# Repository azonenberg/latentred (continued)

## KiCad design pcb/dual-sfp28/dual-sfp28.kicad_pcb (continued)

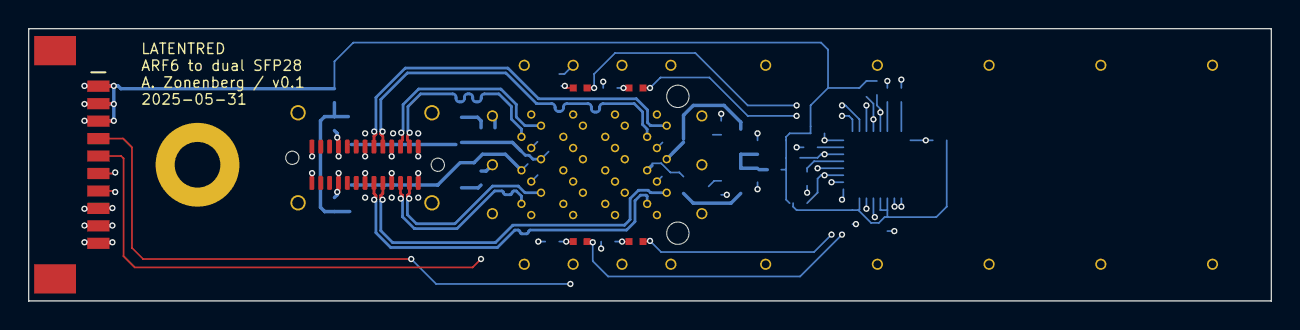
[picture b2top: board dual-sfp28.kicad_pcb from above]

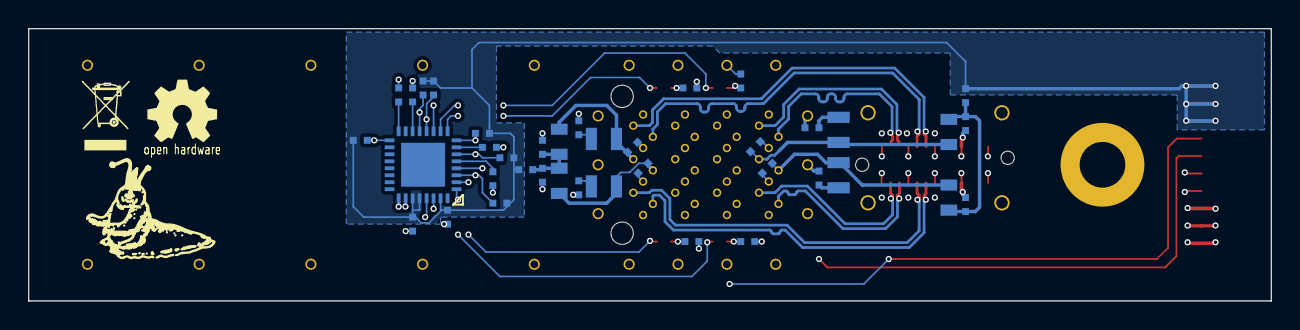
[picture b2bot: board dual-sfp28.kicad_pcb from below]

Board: 4 copper layers, 89.0 x 19.5 mm, 50 parts (42 on the bottom side), 48 nets.

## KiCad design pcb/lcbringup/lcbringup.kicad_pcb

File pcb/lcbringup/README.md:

# lcbringup

This is a bringup test fixture for validating the line card (in conjunction with my kup-lulz XCKU5P FPGA board) and not intended to be part of the final LATENTED system.

Known errata: MDIO and MDC are on ball locations that are NC in the 7a35t FGG484 package. Reworked board connecting MDIO to the SPI pins on the adjacent bank and added external level shifters.

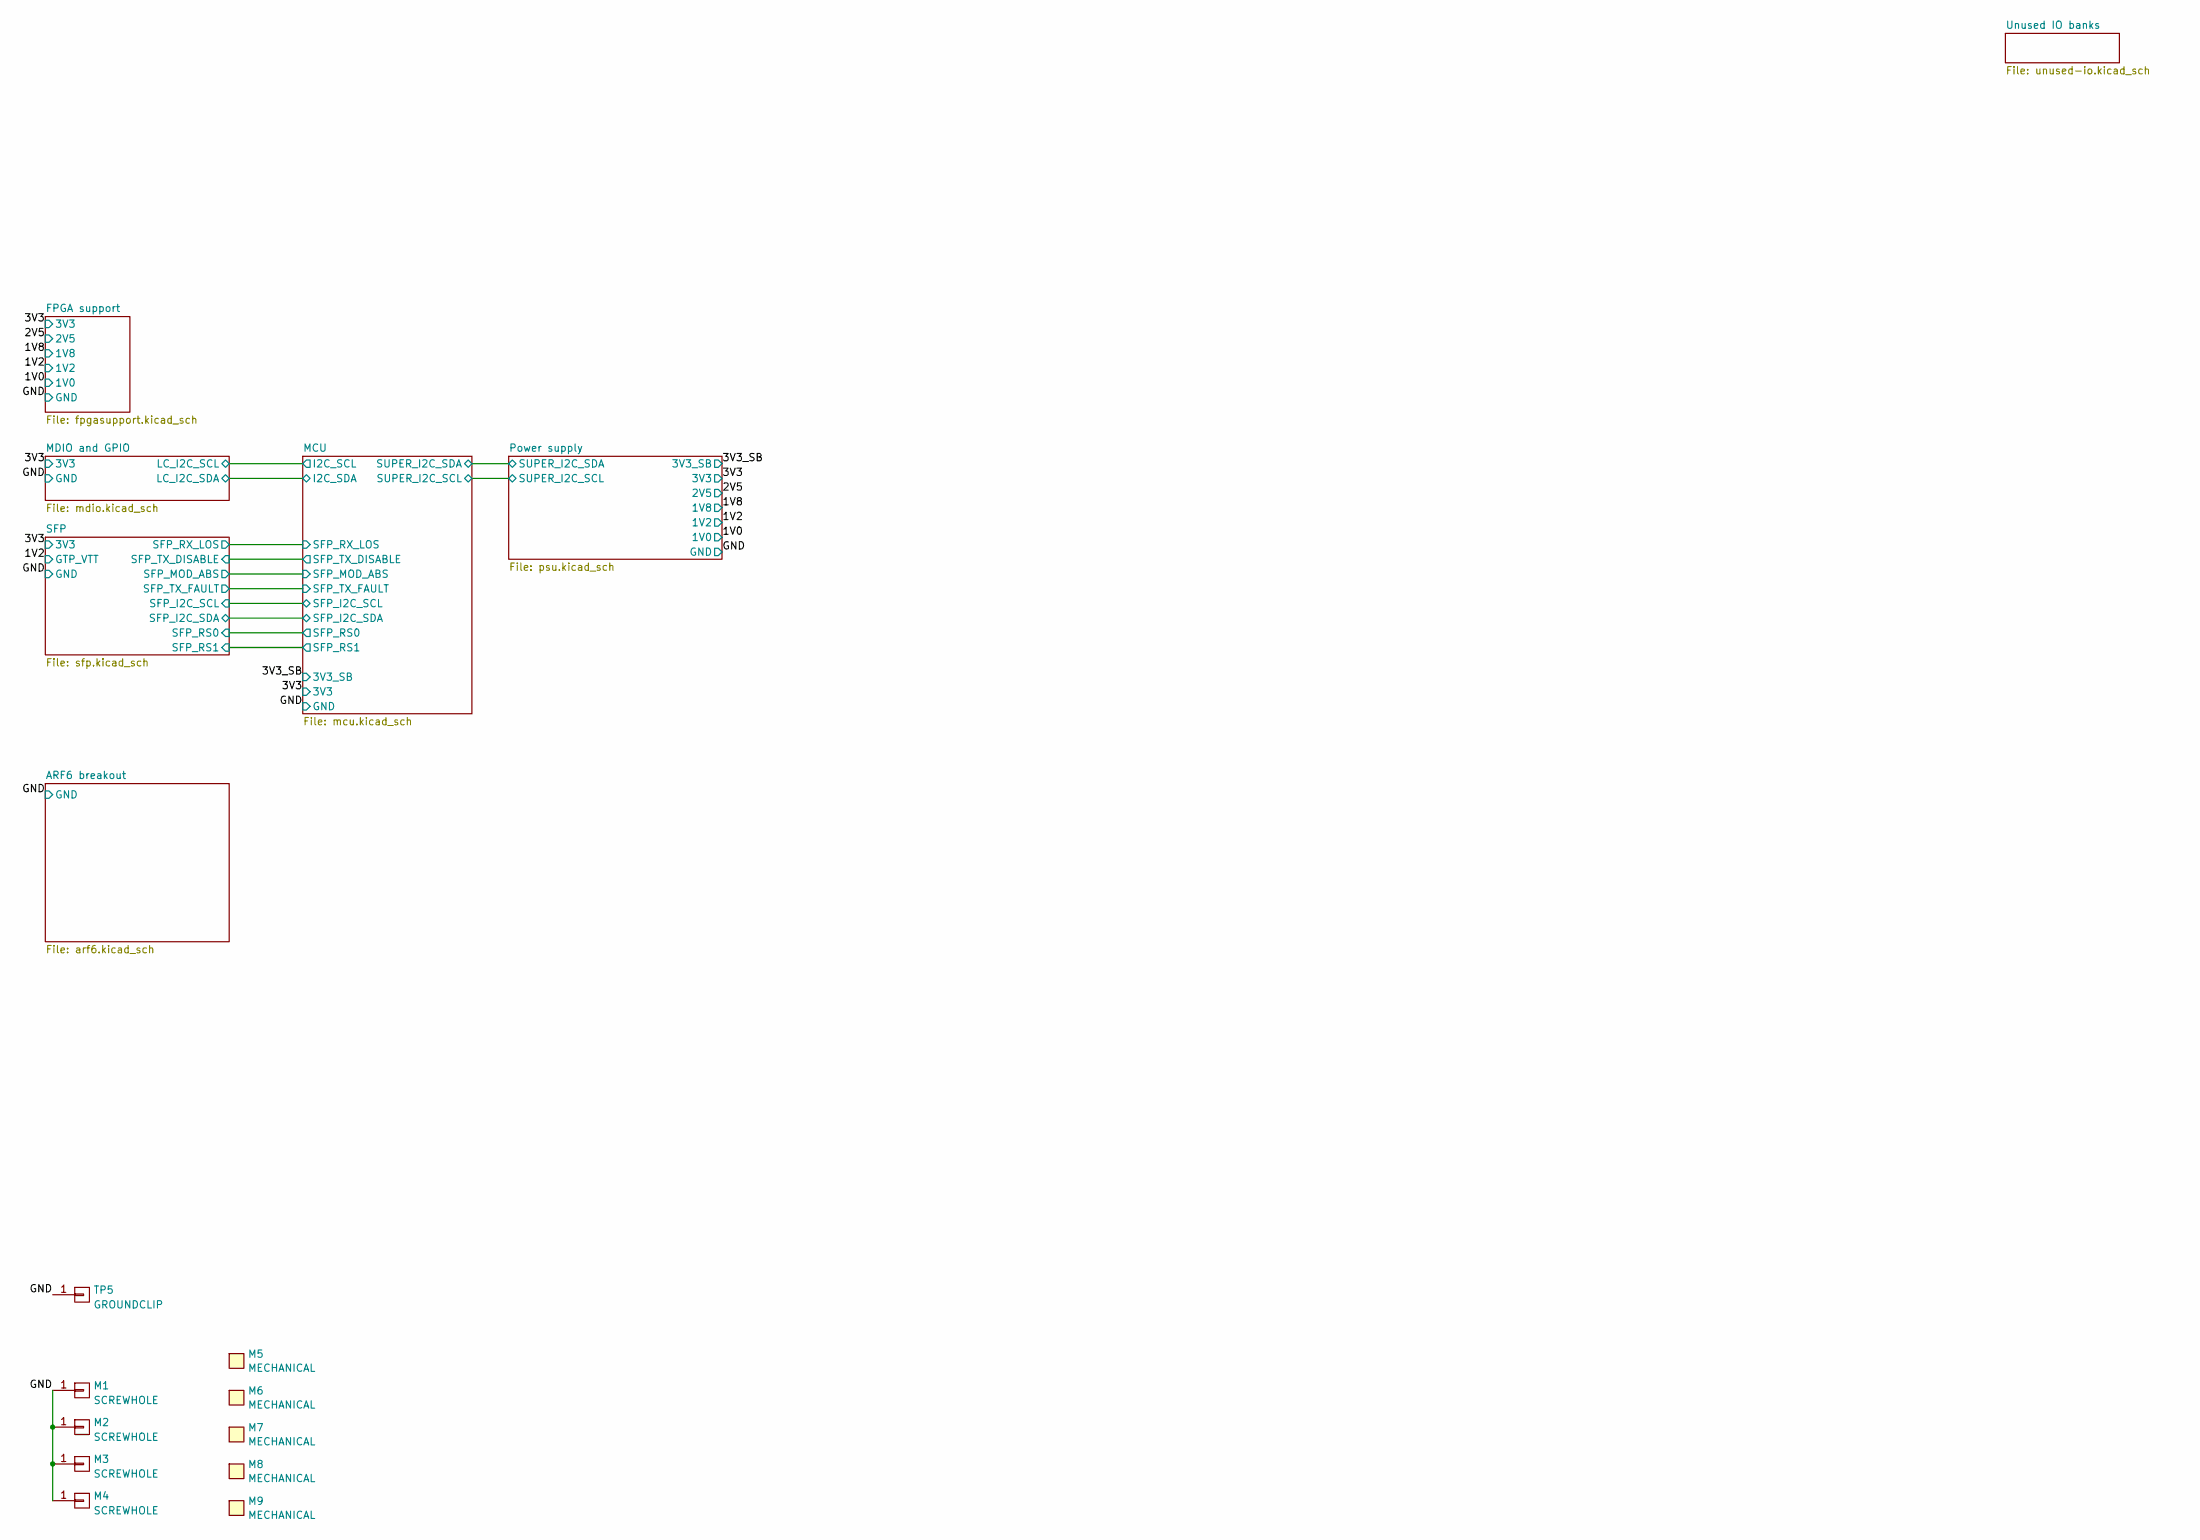
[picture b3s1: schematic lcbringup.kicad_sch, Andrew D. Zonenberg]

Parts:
M1, M2, M3, M4: SCREWHOLE; MECHANICAL_CLEARANCEHOLE_4_40
M5: MECHANICAL; LONGTHING-1200DPI
M6: MECHANICAL; LOGO_ESD_SENSITIVE_7MM
M7: MECHANICAL; Logo_silk_OSHW_6x6mm
M8: MECHANICAL; Logo_silk_ROHS_5x2.8mm
M9: MECHANICAL; Logo_silk_WEEE_3.4x5mm
TP5: GROUNDCLIP; TESTPOINT_SMT_KEYSTONE_5016

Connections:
/GND: M1.1, M2.1, M3.1, M4.1, TP5.1; also elsewhere on the board

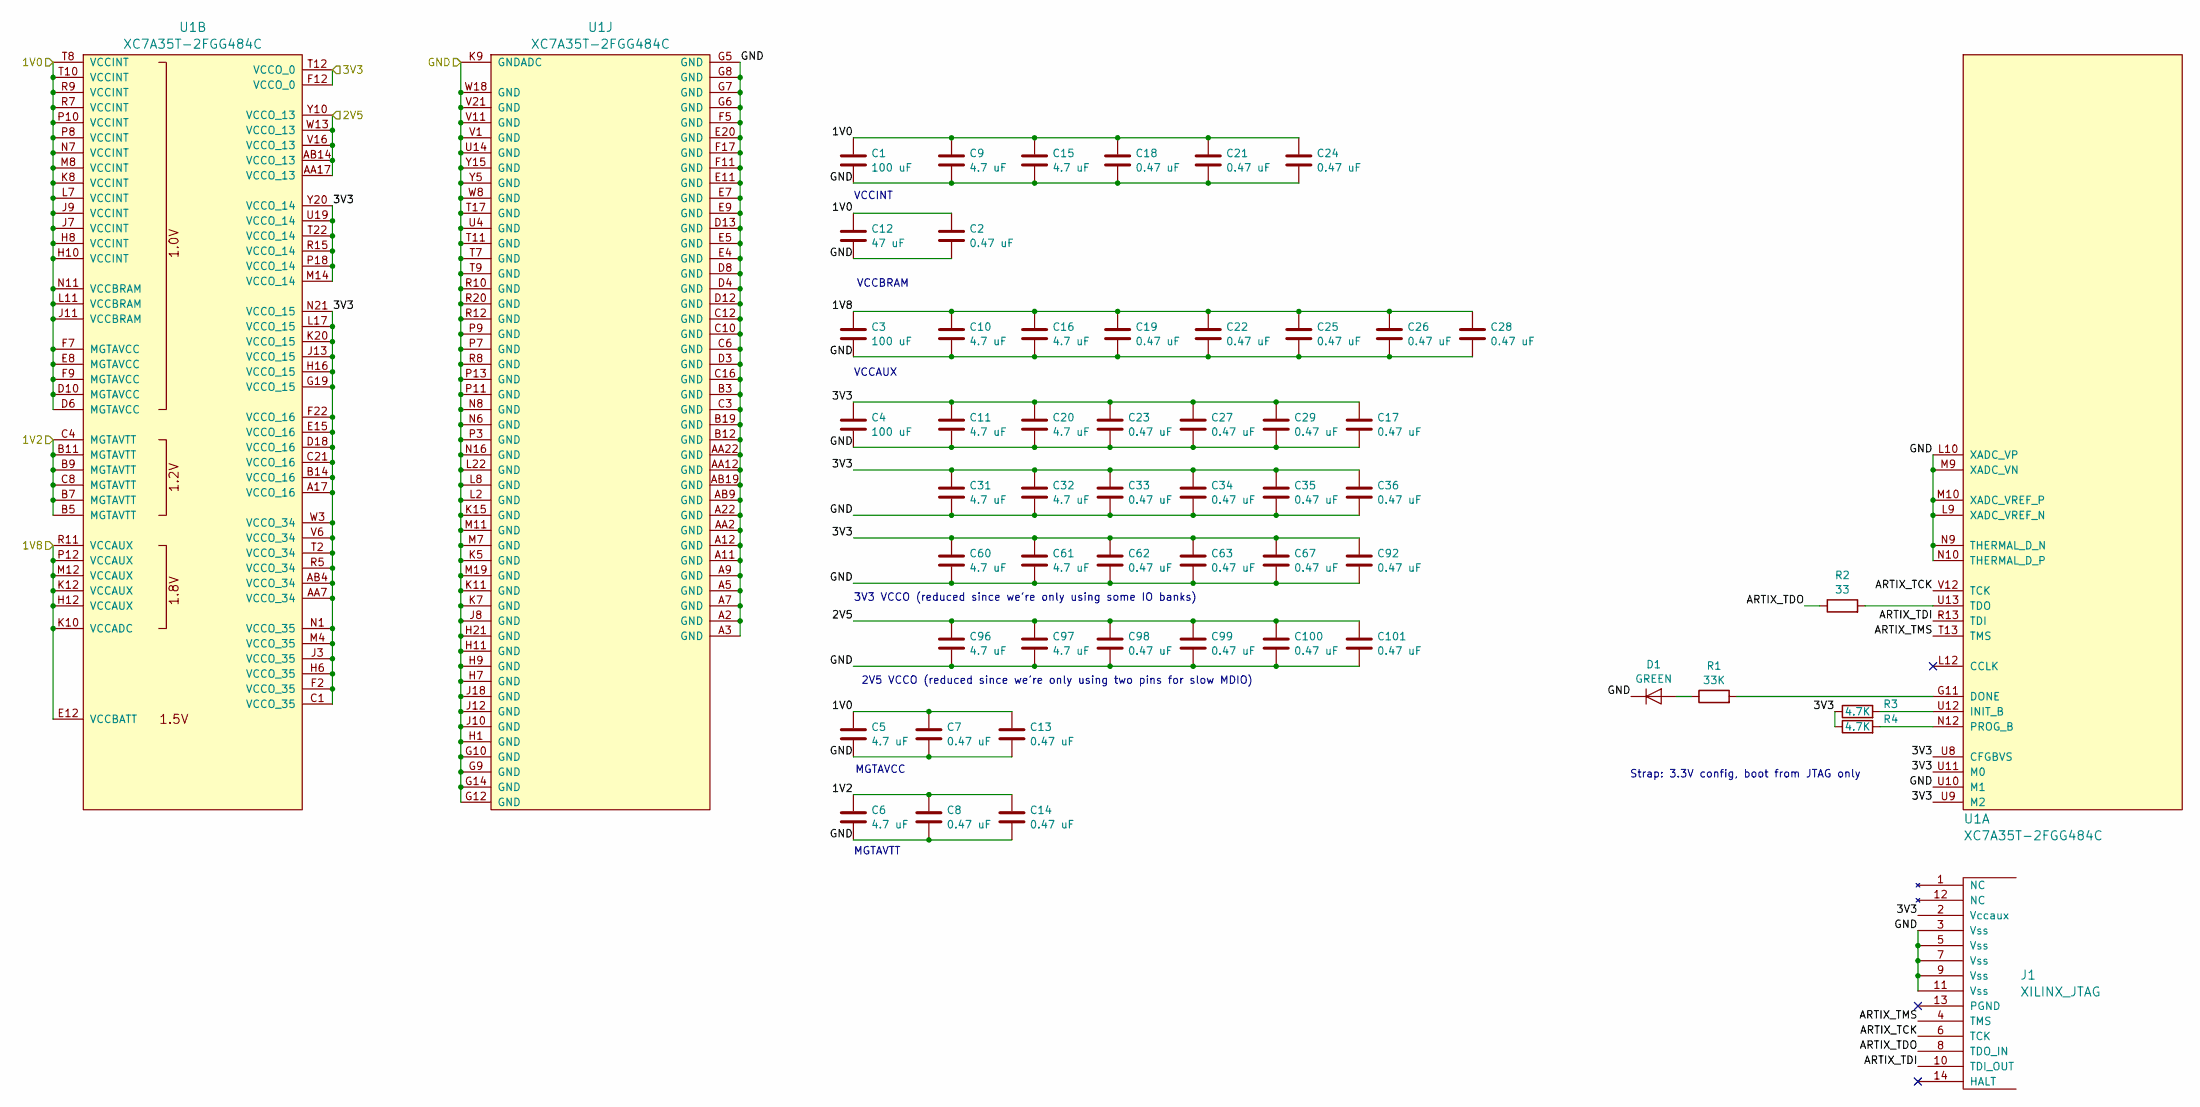
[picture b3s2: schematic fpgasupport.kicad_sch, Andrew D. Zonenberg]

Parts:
C1, C3, C4: 100 uF; EIA_1210_CAP_NOSILK
C2, C7, C8, C13, C14, C17, C18, C19, C21, C22, C23, C24, C25, C26, C27, C28, C29, C33, C34, C35, C36, C62, C63, C67, C92, C98, C99, C100, C101: 0.47 uF; EIA_0402_CAP_NOSILK
C5, C6, C9, C10, C11, C15, C16, C20, C31, C32, C60, C61, C96, C97: 4.7 uF; EIA_0603_CAP_NOSILK
C12: 47 uF; EIA_1210_CAP_NOSILK
D1: GREEN; EIA_0402_LED
J1: XILINX_JTAG; XILINX_JTAG_PTH_MOLEX_0878311420
R1: 33K; EIA_0402_RES_NOSILK
R2: 33; EIA_0402_RES_NOSILK
R3, R4: 4.7K; EIA_0402_RES_NOSILK
U1: XC7A35T-2FGG484C; BGA_484_22x22_FULLARRAY_1MM

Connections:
/1V0: C1.1, C2.1, C5.1, C7.1, C9.1, C12.1, C13.1, C15.1, C18.1, C21.1, C24.1, U1.D6 (MGTAVCC), U1.D10 (MGTAVCC), U1.E8 (MGTAVCC), U1.F7 (MGTAVCC), U1.F9 (MGTAVCC), U1.H8 (VCCINT), U1.H10 (VCCINT), U1.J7 (VCCINT), U1.J9 (VCCINT), U1.J11 (VCCBRAM), U1.K8 (VCCINT), U1.L7 (VCCINT), U1.L11 (VCCBRAM), U1.M8 (VCCINT), U1.N7 (VCCINT), U1.N11 (VCCBRAM), U1.P8 (VCCINT), U1.P10 (VCCINT), U1.R7 (VCCINT), U1.R9 (VCCINT), U1.T8 (VCCINT), U1.T10 (VCCINT); also elsewhere on the board
/1V2: C6.1, C8.1, C14.1, U1.B5 (MGTAVTT), U1.B7 (MGTAVTT), U1.B9 (MGTAVTT), U1.B11 (MGTAVTT), U1.C4 (MGTAVTT), U1.C8 (MGTAVTT); also elsewhere on the board
/1V8: C3.1, C10.1, C16.1, C19.1, C22.1, C25.1, C26.1, C28.1, U1.E12 (VCCBATT), U1.H12 (VCCAUX), U1.K10 (VCCADC), U1.K12 (VCCAUX), U1.M12 (VCCAUX), U1.P12 (VCCAUX), U1.R11 (VCCAUX); also elsewhere on the board
/2V5: C96.1, C97.1, C98.1, C99.1, C100.1, C101.1, U1.AA17 (VCCO_13), U1.AB14 (VCCO_13), U1.V16 (VCCO_13), U1.W13 (VCCO_13), U1.Y10 (VCCO_13); also elsewhere on the board
/3V3: C4.1, C11.1, C17.1, C20.1, C23.1, C27.1, C29.1, C31.1, C32.1, C33.1, C34.1, C35.1, C36.1, C60.1, C61.1, C62.1, C63.1, C67.1, C92.1, J1.2 (Vccaux), R3.1, R4.1, U1.A17 (VCCO_16), U1.AA7 (VCCO_34), U1.AB4 (VCCO_34), U1.B14 (VCCO_16), U1.C1 (VCCO_35), U1.C21 (VCCO_16), U1.D18 (VCCO_16), U1.E15 (VCCO_16), U1.F2 (VCCO_35), U1.F12 (VCCO_0), U1.F22 (VCCO_16), U1.G19 (VCCO_15), U1.H6 (VCCO_35), U1.H16 (VCCO_15), U1.J3 (VCCO_35), U1.J13 (VCCO_15), U1.K20 (VCCO_15), U1.L17 (VCCO_15), U1.M4 (VCCO_35), U1.M14 (VCCO_14), U1.N1 (VCCO_35), U1.N21 (VCCO_15), U1.P18 (VCCO_14), U1.R5 (VCCO_34), U1.R15 (VCCO_14), U1.T2 (VCCO_34), U1.T12 (VCCO_0), U1.T22 (VCCO_14), U1.U8 (CFGBVS), U1.U9 (M2), U1.U11 (M0), U1.U19 (VCCO_14), U1.V6 (VCCO_34), U1.W3 (VCCO_34), U1.Y20 (VCCO_14); also elsewhere on the board
/FPGA support/ARTIX_TCK: J1.6 (TCK), U1.V12 (TCK)
/FPGA support/ARTIX_TDI: J1.10 (TDI_OUT), U1.R13 (TDI)
/FPGA support/ARTIX_TDO: J1.8 (TDO_IN), R2.1
/FPGA support/ARTIX_TMS: J1.4 (TMS), U1.T13 (TMS)
/GND: C1.2, C2.2, C3.2, C4.2, C5.2, C6.2, C7.2, C8.2, C9.2, C10.2, C11.2, C12.2, C13.2, C14.2, C15.2, C16.2, C17.2, C18.2, C19.2, C20.2, C21.2, C22.2, C23.2, C24.2, C25.2, C26.2, C27.2, C28.2, C29.2, C31.2, C32.2, C33.2, C34.2, C35.2, C36.2, C60.2, C61.2, C62.2, C63.2, C67.2, C92.2, C96.2, C97.2, C98.2, C99.2, C100.2, C101.2, D1.1 (K), J1.3 (Vss), J1.5 (Vss), J1.7 (Vss), J1.9 (Vss), J1.11 (Vss), U1.A2 (GND), U1.A3 (GND), U1.A5 (GND), U1.A7 (GND), U1.A9 (GND), U1.A11 (GND), U1.A12 (GND), U1.A22 (GND), U1.AA2 (GND), U1.AA12 (GND), U1.AA22 (GND), U1.AB9 (GND), U1.AB19 (GND), U1.B3 (GND), U1.B12 (GND), U1.B19 (GND), U1.C3 (GND), U1.C6 (GND), U1.C10 (GND), U1.C12 (GND), U1.C16 (GND), U1.D3 (GND), U1.D4 (GND), U1.D8 (GND), U1.D12 (GND), U1.D13 (GND), U1.E4 (GND), U1.E5 (GND), U1.E7 (GND), U1.E9 (GND), U1.E11 (GND), U1.E20 (GND), U1.F5 (GND), U1.F11 (GND), U1.F17 (GND), U1.G5 (GND), U1.G6 (GND), U1.G7 (GND), U1.G8 (GND), U1.G9 (GND), U1.G10 (GND), U1.G12 (GND), U1.G14 (GND), U1.H1 (GND), U1.H7 (GND), U1.H9 (GND), U1.H11 (GND), U1.H21 (GND), U1.J8 (GND), U1.J10 (GND), U1.J12 (GND), U1.J18 (GND), U1.K5 (GND), U1.K7 (GND), U1.K9 (GNDADC), U1.K11 (GND), U1.K15 (GND), U1.L2 (GND), U1.L8 (GND), U1.L9 (XADC_VREF_N), U1.L10 (XADC_VP), U1.L22 (GND), U1.M7 (GND), U1.M9 (XADC_VN), U1.M10 (XADC_VREF_P), U1.M11 (GND), U1.M19 (GND), U1.N6 (GND), U1.N8 (GND), U1.N9 (THERMAL_D_N), U1.N10 (THERMAL_D_P), U1.N16 (GND), U1.P3 (GND), U1.P7 (GND), U1.P9 (GND), U1.P11 (GND), U1.P13 (GND), U1.R8 (GND), U1.R10 (GND), U1.R12 (GND), U1.R20 (GND), U1.T7 (GND), U1.T9 (GND), U1.T11 (GND), U1.T17 (GND), U1.U4 (GND), U1.U10 (M1), U1.U14 (GND), U1.V1 (GND), U1.V11 (GND), U1.V21 (GND), U1.W8 (GND), U1.W18 (GND), U1.Y5 (GND), U1.Y15 (GND); also elsewhere on the board
unnamed: D1.2 (A), R1.1
unnamed: R1.2, U1.G11 (DONE)
unnamed: R3.2, U1.U12 (INIT_B)
unnamed: R4.2, U1.N12 (PROG_B)
unnamed: R2.2, U1.U13 (TDO)

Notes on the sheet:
Strap: 3.3V config, boot from JTAG only
2V5 VCCO (reduced since we're only using two pins for slow MDIO)
VCCAUX
VCCINT
3V3 VCCO (reduced since we're only using some IO banks)
MGTAVTT
VCCBRAM
MGTAVCC

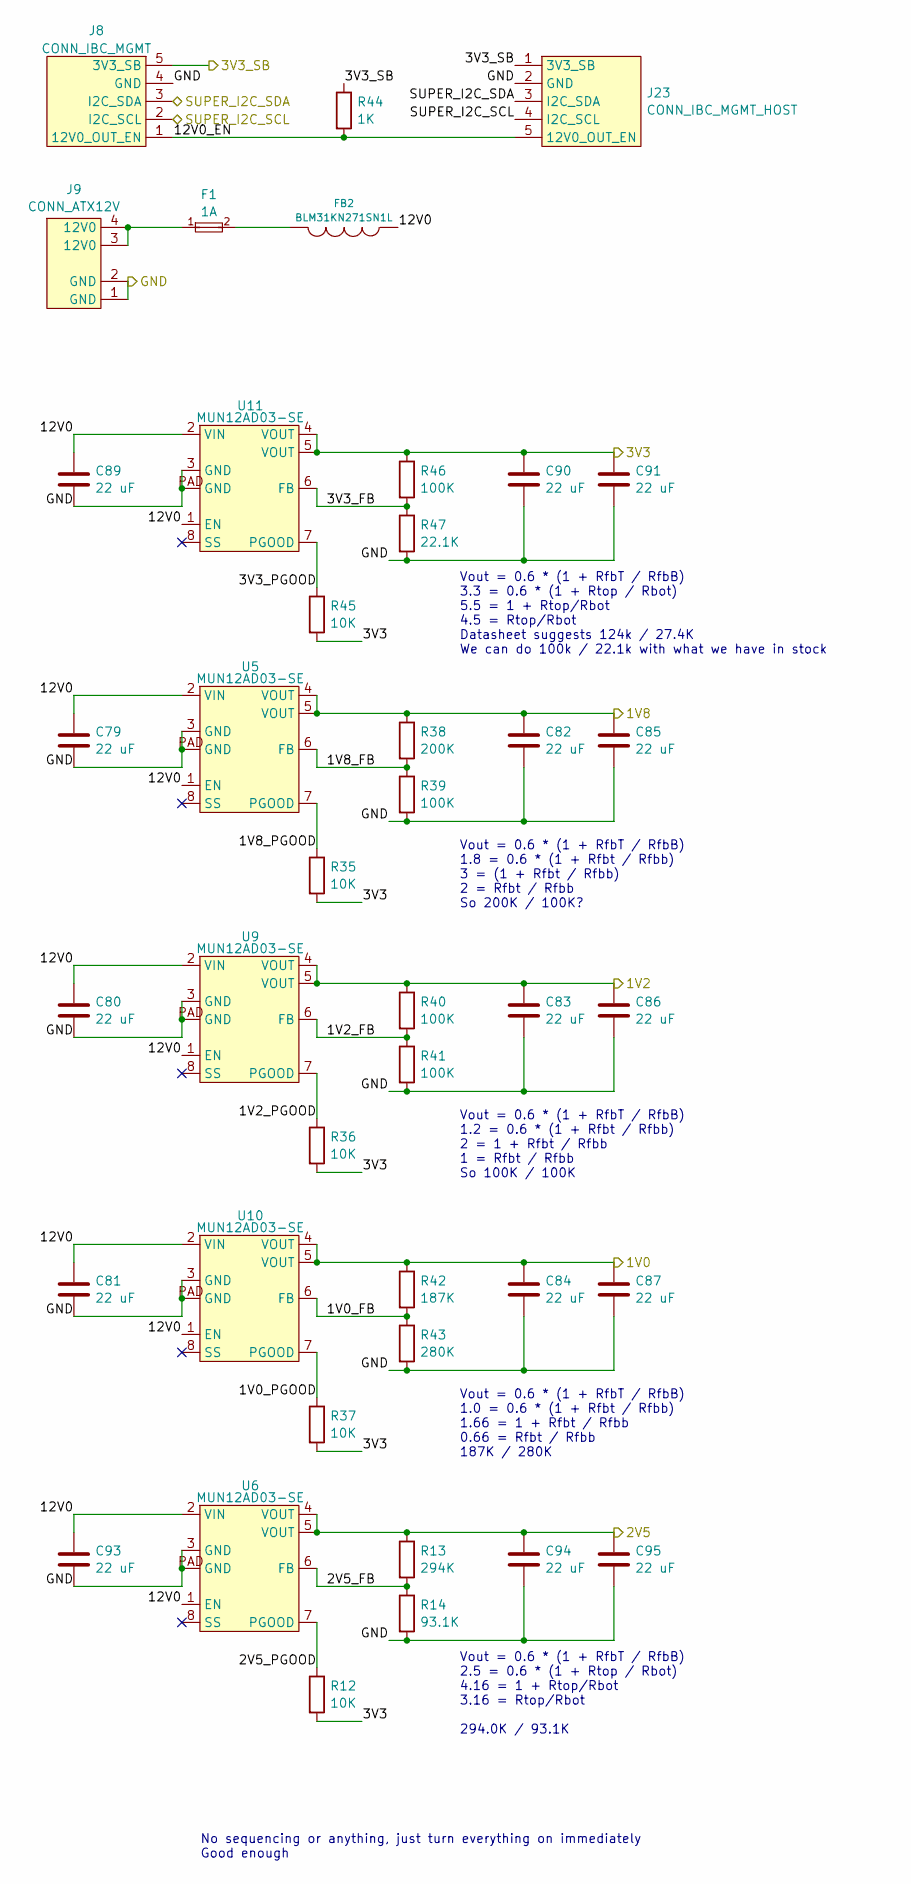
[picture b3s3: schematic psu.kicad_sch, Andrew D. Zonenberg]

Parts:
C79, C80, C81, C89, C93: 22 uF; EIA_1812_CAP_NOSILK
C82, C83, C84, C85, C86, C87, C90, C91, C94, C95: 22 uF; EIA_1210_CAP_NOSILK
F1: 1A; EIA_0402_RES_NOSILK
FB2: BLM31KN271SN1L; EIA_1206_CAP_NOSILK
J8: CONN_IBC_MGMT; CONN_MOLEX_PICOBLADE_5POS_0532610571
J9: CONN_ATX12V; CONN_MOLEX_MINIFITJR_4POS_0039291048
J23: CONN_IBC_MGMT_HOST; CONN_MOLEX_PICOBLADE_5POS_0532610571
R12, R35, R36, R37, R45: 10K; EIA_0402_RES_NOSILK
R13: 294K; EIA_0402_RES_NOSILK
R14: 93.1K; EIA_0402_RES_NOSILK
R38: 200K; EIA_0402_RES_NOSILK
R39, R40, R41, R46: 100K; EIA_0402_RES_NOSILK
R42: 187K; EIA_0402_RES_NOSILK
R43: 280K; EIA_0402_RES_NOSILK
R44: 1K; EIA_0402_RES_NOSILK
R47: 22.1K; EIA_0402_RES_NOSILK
U5, U6, U9, U10, U11: MUN12AD03-SE; MODULE_CYNTEC_MUN12AD03-SE

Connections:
/1V0: C84.1, C87.1, R42.1, U10.4 (VOUT), U10.5 (VOUT); also elsewhere on the board
/1V2: C83.1, C86.1, R40.1, U9.4 (VOUT), U9.5 (VOUT); also elsewhere on the board
/1V8: C82.1, C85.1, R38.1, U5.4 (VOUT), U5.5 (VOUT); also elsewhere on the board
/2V5: C94.1, C95.1, R13.1, U6.4 (VOUT), U6.5 (VOUT); also elsewhere on the board
/3V3: C90.1, C91.1, R12.2, R35.2, R36.2, R37.2, R45.2, R46.1, U11.4 (VOUT), U11.5 (VOUT); also elsewhere on the board
/3V3_SB: J8.5 (3V3_SB), J23.1 (3V3_SB), R44.1; also elsewhere on the board
/GND: C79.2, C80.2, C81.2, C82.2, C83.2, C84.2, C85.2, C86.2, C87.2, C89.2, C90.2, C91.2, C93.2, C94.2, C95.2, J8.4 (GND), J9.1 (GND), J9.2 (GND), J23.2 (GND), R14.2, R39.2, R41.2, R43.2, R47.2, U5.3 (GND), U5.PAD (GND), U6.3 (GND), U6.PAD (GND), U9.3 (GND), U9.PAD (GND), U10.3 (GND), U10.PAD (GND), U11.3 (GND), U11.PAD (GND); also elsewhere on the board
/Power supply/1V0_FB: R42.2, R43.1, U10.6 (FB)
/Power supply/1V0_PGOOD: R37.1, U10.7 (PGOOD)
/Power supply/1V2_FB: R40.2, R41.1, U9.6 (FB)
/Power supply/1V2_PGOOD: R36.1, U9.7 (PGOOD)
/Power supply/1V8_FB: R38.2, R39.1, U5.6 (FB)
/Power supply/1V8_PGOOD: R35.1, U5.7 (PGOOD)
/Power supply/2V5_FB: R13.2, R14.1, U6.6 (FB)
/Power supply/2V5_PGOOD: R12.1, U6.7 (PGOOD)
/Power supply/3V3_FB: R46.2, R47.1, U11.6 (FB)
/Power supply/3V3_PGOOD: R45.1, U11.7 (PGOOD)
/Power supply/12V0: C79.1, C80.1, C81.1, C89.1, C93.1, FB2.1, U5.1 (EN), U5.2 (VIN), U6.1 (EN), U6.2 (VIN), U9.1 (EN), U9.2 (VIN), U10.1 (EN), U10.2 (VIN), U11.1 (EN), U11.2 (VIN)
/Power supply/12V0_EN: J8.1 (12V0_OUT_EN), J23.5 (12V0_OUT_EN), R44.2
/Power supply/SUPER_I2C_SCL: J8.2 (I2C_SCL), J23.4 (I2C_SCL); also elsewhere on the board
/Power supply/SUPER_I2C_SDA: J8.3 (I2C_SDA), J23.3 (I2C_SDA); also elsewhere on the board
unnamed: F1.1, J9.3 (12V0), J9.4 (12V0)
unnamed: F1.2, FB2.2

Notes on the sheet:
Vout = 0.6 * (1 + RfbT / RfbB) 1.2 = 0.6 * (1 + Rfbt / Rfbb) 2 = 1 + Rfbt / Rfbb 1 = Rfbt / Rfbb So 100K / 100K
Vout = 0.6 * (1 + RfbT / RfbB) 2.5 = 0.6 * (1 + Rtop / Rbot) 4.16 = 1 + Rtop/Rbot 3.16 = Rtop/Rbot 294.0K / 93.1K
No sequencing or anything, just turn everything on immediately Good enough
Vout = 0.6 * (1 + RfbT / RfbB) 3.3 = 0.6 * (1 + Rtop / Rbot) 5.5 = 1 + Rtop/Rbot 4.5 = Rtop/Rbot Datasheet suggests 124k / 27.4K We can do 100k / 22.1k with what we have in stock
Vout = 0.6 * (1 + RfbT / RfbB) 1.0 = 0.6 * (1 + Rfbt / Rfbb) 1.66 = 1 + Rfbt / Rfbb 0.66 = Rfbt / Rfbb 187K / 280K
Vout = 0.6 * (1 + RfbT / RfbB) 1.8 = 0.6 * (1 + Rfbt / Rfbb) 3 = (1 + Rfbt / Rfbb) 2 = Rfbt / Rfbb So 200K / 100K?

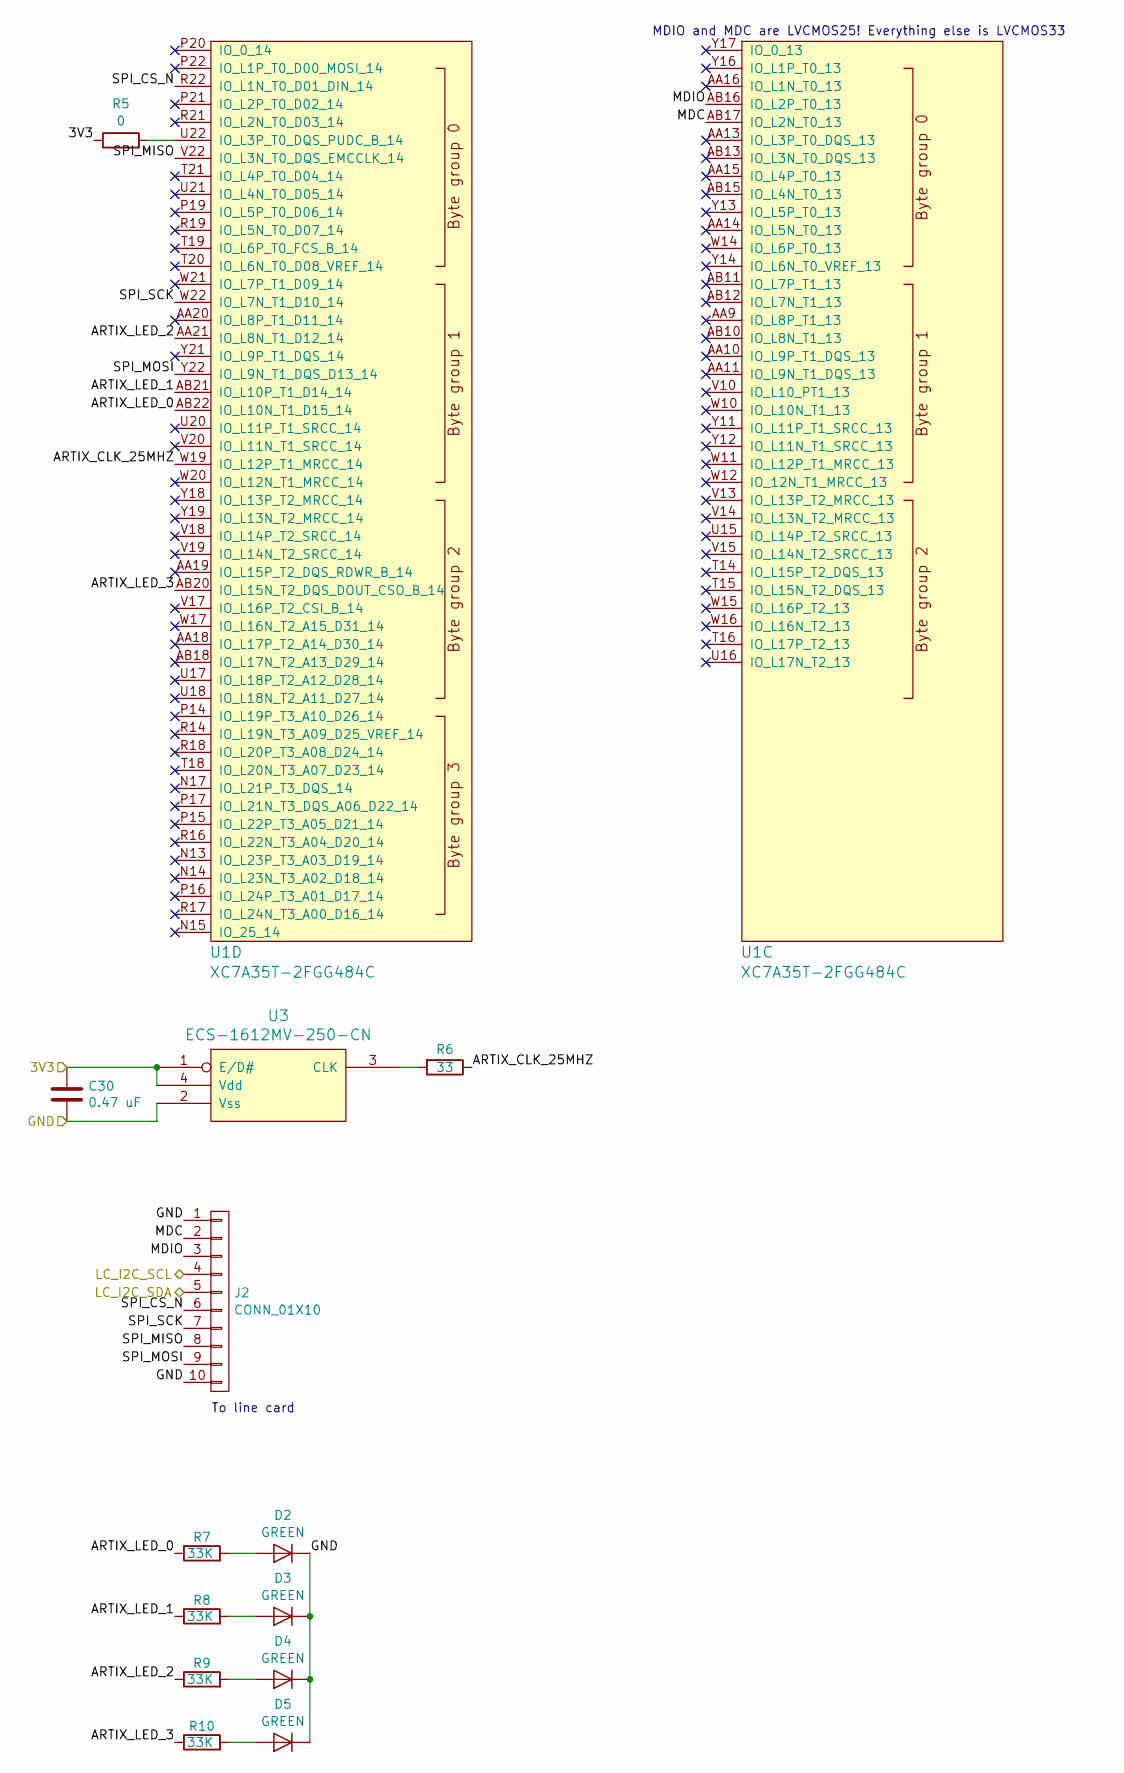
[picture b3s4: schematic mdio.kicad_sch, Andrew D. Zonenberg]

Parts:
C30: 0.47 uF; EIA_0402_CAP_NOSILK
D2, D3, D4, D5: GREEN; EIA_0402_LED
J2: CONN_01X10; CONN_MOLEX_PICOBLADE_10POS_0532611071
R5: 0; EIA_0402_RES_NOSILK
R6: 33; EIA_0402_RES_NOSILK
R7, R8, R9, R10: 33K; EIA_0402_RES_NOSILK
U1: XC7A35T-2FGG484C; BGA_484_22x22_FULLARRAY_1MM
U3: ECS-1612MV-250-CN; OSCILLATOR_1.6x1.2

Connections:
/3V3: C30.1, R5.1, U3.1 (E/D#), U3.4 (Vdd); also elsewhere on the board
/GND: C30.2, D2.1 (K), D3.1 (K), D4.1 (K), D5.1 (K), J2.1, J2.10, U3.2 (Vss); also elsewhere on the board
/MCU/I2C_SCL: J2.4; also elsewhere on the board
/MCU/I2C_SDA: J2.5; also elsewhere on the board
/MDIO and GPIO/ARTIX_CLK_25MHZ: R6.1, U1.W19 (IO_L12P_T1_MRCC_14)
/MDIO and GPIO/ARTIX_LED_0: R7.1, U1.AB22 (IO_L10N_T1_D15_14)
/MDIO and GPIO/ARTIX_LED_1: R8.1, U1.AB21 (IO_L10P_T1_D14_14)
/MDIO and GPIO/ARTIX_LED_2: R9.1, U1.AA21 (IO_L8N_T1_D12_14)
/MDIO and GPIO/ARTIX_LED_3: R10.1, U1.AB20 (IO_L15N_T2_DQS_DOUT_CSO_B_14)
/MDIO and GPIO/MDC: J2.2, U1.AB17 (IO_L2N_T0_13)
/MDIO and GPIO/MDIO: J2.3, U1.AB16 (IO_L2P_T0_13)
/MDIO and GPIO/SPI_CS_N: J2.6, U1.R22 (IO_L1N_T0_D01_DIN_14)
/MDIO and GPIO/SPI_MISO: J2.8, U1.V22 (IO_L3N_T0_DQS_EMCCLK_14)
/MDIO and GPIO/SPI_MOSI: J2.9, U1.Y22 (IO_L9N_T1_DQS_D13_14)
/MDIO and GPIO/SPI_SCK: J2.7, U1.W22 (IO_L7N_T1_D10_14)
unnamed: D2.2 (A), R7.2
unnamed: D3.2 (A), R8.2
unnamed: D4.2 (A), R9.2
unnamed: D5.2 (A), R10.2
unnamed: R5.2, U1.U22 (IO_L3P_T0_DQS_PUDC_B_14)
unnamed: R6.2, U3.3 (CLK)

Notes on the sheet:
To line card
MDIO and MDC are LVCMOS25! Everything else is LVCMOS33

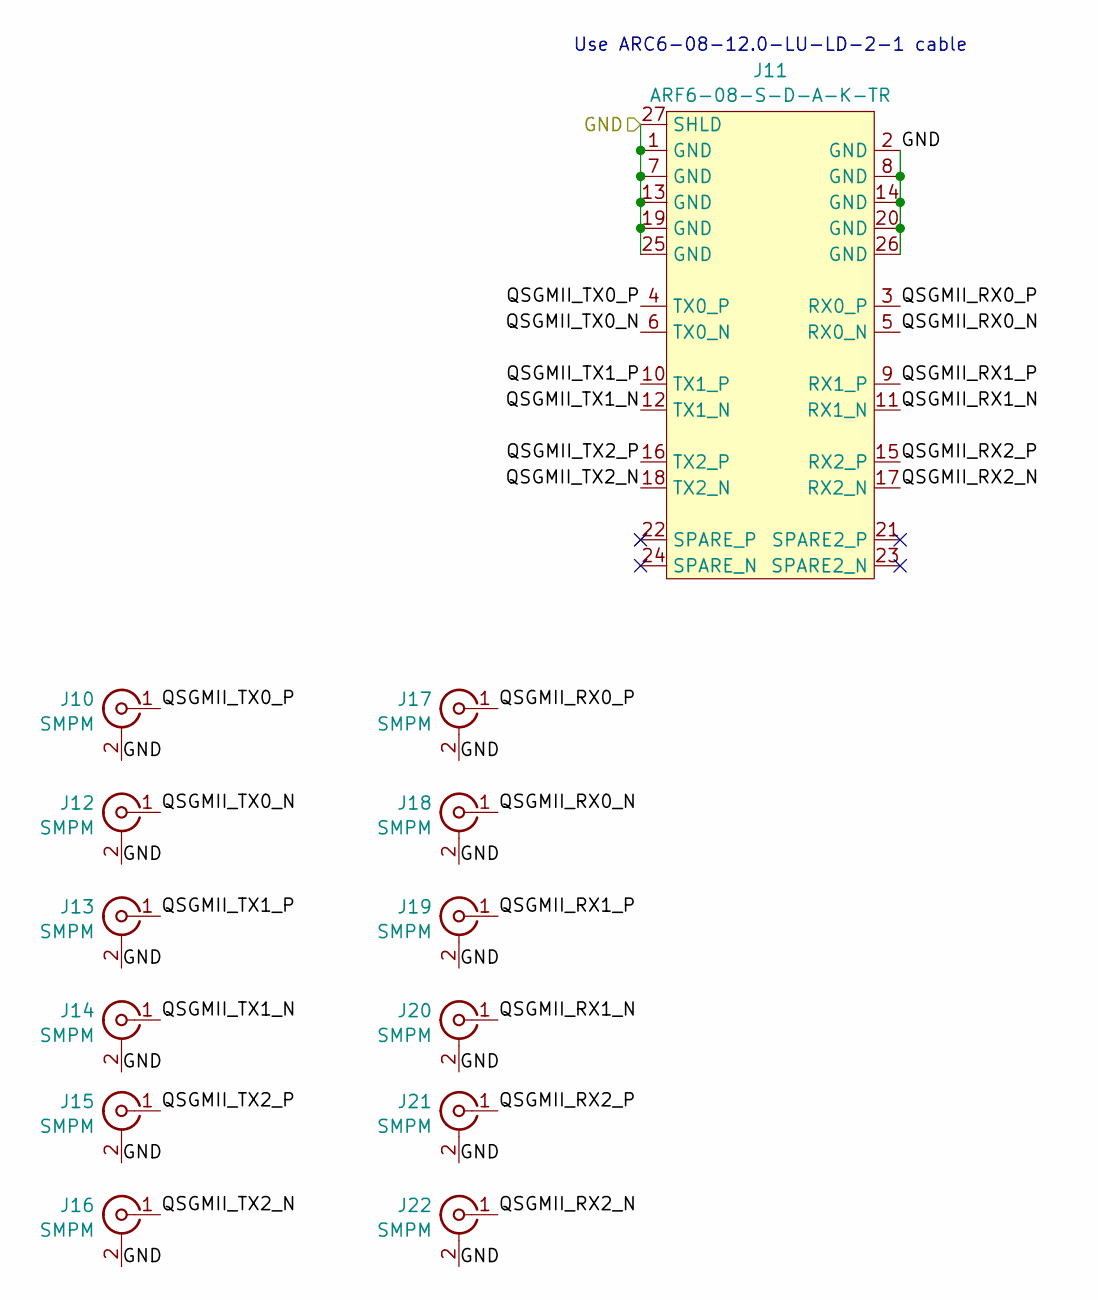
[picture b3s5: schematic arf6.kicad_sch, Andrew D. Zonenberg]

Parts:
J10, J12, J13, J14, J15, J16, J17, J18, J19, J20, J21, J22: SMPM; CONN_SMPM_AMPHENOL_C925-197J-51PT
J11: ARF6-08-S-D-A-K-TR; CONN_SAMTEC_ARF6-08-S-D-A-K-TR

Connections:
/ARF6 breakout/QSGMII_RX0_N: J11.5 (RX0_N), J18.1 (In)
/ARF6 breakout/QSGMII_RX0_P: J11.3 (RX0_P), J17.1 (In)
/ARF6 breakout/QSGMII_RX1_N: J11.11 (RX1_N), J20.1 (In)
/ARF6 breakout/QSGMII_RX1_P: J11.9 (RX1_P), J19.1 (In)
/ARF6 breakout/QSGMII_RX2_N: J11.17 (RX2_N), J22.1 (In)
/ARF6 breakout/QSGMII_RX2_P: J11.15 (RX2_P), J21.1 (In)
/ARF6 breakout/QSGMII_TX0_N: J11.6 (TX0_N), J12.1 (In)
/ARF6 breakout/QSGMII_TX0_P: J10.1 (In), J11.4 (TX0_P)
/ARF6 breakout/QSGMII_TX1_N: J11.12 (TX1_N), J14.1 (In)
/ARF6 breakout/QSGMII_TX1_P: J11.10 (TX1_P), J13.1 (In)
/ARF6 breakout/QSGMII_TX2_N: J11.18 (TX2_N), J16.1 (In)
/ARF6 breakout/QSGMII_TX2_P: J11.16 (TX2_P), J15.1 (In)
/GND: J10.2 (Ext), J11.1 (GND), J11.2 (GND), J11.7 (GND), J11.8 (GND), J11.13 (GND), J11.14 (GND), J11.19 (GND), J11.20 (GND), J11.25 (GND), J11.26 (GND), J11.27 (SHLD), J12.2 (Ext), J13.2 (Ext), J14.2 (Ext), J15.2 (Ext), J16.2 (Ext), J17.2 (Ext), J18.2 (Ext), J19.2 (Ext), J20.2 (Ext), J21.2 (Ext), J22.2 (Ext); also elsewhere on the board

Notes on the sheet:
Use ARC6-08-12.0-LU-LD-2-1 cable

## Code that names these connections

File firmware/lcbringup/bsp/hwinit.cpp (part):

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
void BSP_InitUART()
{
	//Initialize the UART for local console: 115.2 Kbps using PA12 for UART4 transmit and PA11 for UART4 receive
	//TODO: nice interface for enabling UART interrupts
	static GPIOPin uart_tx(&GPIOA, 12, GPIOPin::MODE_PERIPHERAL, GPIOPin::SLEW_SLOW, 6);
	static GPIOPin uart_rx(&GPIOA, 11, GPIOPin::MODE_PERIPHERAL, GPIOPin::SLEW_SLOW, 6);

	//Enable the UART interrupt
	NVIC_EnableIRQ(52);
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	g_log("Initializing FMC...\n");
	LogIndenter li(g_log);

	static GPIOPin fmc_ad0(&GPIOD, 14, GPIOPin::MODE_PERIPHERAL, GPIOPin::SLEW_VERYFAST, 12);
	static GPIOPin fmc_ad1(&GPIOD, 15, GPIOPin::MODE_PERIPHERAL, GPIOPin::SLEW_VERYFAST, 12);
	static GPIOPin fmc_ad2(&GPIOD, 0, GPIOPin::MODE_PERIPHERAL, GPIOPin::SLEW_VERYFAST, 12);
	static GPIOPin fmc_ad3(&GPIOD, 1, GPIOPin::MODE_PERIPHERAL, GPIOPin::SLEW_VERYFAST, 12);
	static GPIOPin fmc_ad4(&GPIOE, 7, GPIOPin::MODE_PERIPHERAL, GPIOPin::SLEW_VERYFAST, 12);
	static GPIOPin fmc_ad5(&GPIOE, 8, GPIOPin::MODE_PERIPHERAL, GPIOPin::SLEW_VERYFAST, 12);
	static GPIOPin fmc_ad6(&GPIOE, 9, GPIOPin::MODE_PERIPHERAL, GPIOPin::SLEW_VERYFAST, 12);
	static GPIOPin fmc_ad7(&GPIOE, 10, GPIOPin::MODE_PERIPHERAL, GPIOPin::SLEW_VERYFAST, 12);
	static GPIOPin fmc_ad8(&GPIOE, 11, GPIOPin::MODE_PERIPHERAL, GPIOPin::SLEW_VERYFAST, 12);
	static GPIOPin fmc_ad9(&GPIOA, 5, GPIOPin::MODE_PERIPHERAL, GPIOPin::SLEW_VERYFAST, 12);
	static GPIOPin fmc_ad10(&GPIOB, 14, GPIOPin::MODE_PERIPHERAL, GPIOPin::SLEW_VERYFAST, 12);
	static GPIOPin fmc_ad11(&GPIOE, 14, GPIOPin::MODE_PERIPHERAL, GPIOPin::SLEW_VERYFAST, 12);
	static GPIOPin fmc_ad12(&GPIOE, 15, GPIOPin::MODE_PERIPHERAL, GPIOPin::SLEW_VERYFAST, 12);
	static GPIOPin fmc_ad13(&GPIOD, 8, GPIOPin::MODE_PERIPHERAL, GPIOPin::SLEW_VERYFAST, 12);
	static GPIOPin fmc_ad14(&GPIOD, 9, GPIOPin::MODE_PERIPHERAL, GPIOPin::SLEW_VERYFAST, 12);
	static GPIOPin fmc_ad15(&GPIOD, 10, GPIOPin::MODE_PERIPHERAL, GPIOPin::SLEW_VERYFAST, 12);

	static GPIOPin fmc_a16(&GPIOD, 11, GPIOPin::MODE_PERIPHERAL, GPIOPin::SLEW_VERYFAST, 12);
	static GPIOPin fmc_a17(&GPIOD, 12, GPIOPin::MODE_PERIPHERAL, GPIOPin::SLEW_VERYFAST, 12);
	static GPIOPin fmc_a18(&GPIOD, 13, GPIOPin::MODE_PERIPHERAL, GPIOPin::SLEW_VERYFAST, 12);
	static GPIOPin fmc_a19(&GPIOE, 3, GPIOPin::MODE_PERIPHERAL, GPIOPin::SLEW_VERYFAST, 12);
	static GPIOPin fmc_a20(&GPIOE, 4, GPIOPin::MODE_PERIPHERAL, GPIOPin::SLEW_VERYFAST, 12);
	static GPIOPin fmc_a21(&GPIOE, 5, GPIOPin::MODE_PERIPHERAL, GPIOPin::SLEW_VERYFAST, 12);
	static GPIOPin fmc_a22(&GPIOE, 6, GPIOPin::MODE_PERIPHERAL, GPIOPin::SLEW_VERYFAST, 12);
	static GPIOPin fmc_a23(&GPIOE, 2, GPIOPin::MODE_PERIPHERAL, GPIOPin::SLEW_VERYFAST, 12);
	static GPIOPin fmc_a24(&GPIOG, 13, GPIOPin::MODE_PERIPHERAL, GPIOPin::SLEW_VERYFAST, 12);
	static GPIOPin fmc_a25(&GPIOG, 14, GPIOPin::MODE_PERIPHERAL, GPIOPin::SLEW_VERYFAST, 12);

	static GPIOPin fmc_nl_nadv(&GPIOB, 7, GPIOPin::MODE_PERIPHERAL, GPIOPin::SLEW_VERYFAST, 12);
	static GPIOPin fmc_nwait(&GPIOC, 6, GPIOPin::MODE_PERIPHERAL, GPIOPin::SLEW_VERYFAST, 9);
	static GPIOPin fmc_ne1(&GPIOC, 7, GPIOPin::MODE_PERIPHERAL, GPIOPin::SLEW_VERYFAST, 9);
	static GPIOPin fmc_ne3(&GPIOG, 6, GPIOPin::MODE_PERIPHERAL, GPIOPin::SLEW_VERYFAST, 12);
	static GPIOPin fmc_clk(&GPIOD, 3, GPIOPin::MODE_PERIPHERAL, GPIOPin::SLEW_VERYFAST, 12);
	static GPIOPin fmc_noe(&GPIOD, 4, GPIOPin::MODE_PERIPHERAL, GPIOPin::SLEW_VERYFAST, 12);
	static GPIOPin fmc_nwe(&GPIOD, 5, GPIOPin::MODE_PERIPHERAL, GPIOPin::SLEW_VERYFAST, 12);
	static GPIOPin fmc_nbl0(&GPIOE, 0, GPIOPin::MODE_PERIPHERAL, GPIOPin::SLEW_VERYFAST, 12);
	static GPIOPin fmc_nbl1(&GPIOE, 1, GPIOPin::MODE_PERIPHERAL, GPIOPin::SLEW_VERYFAST, 12);

	//Add a pullup on NWAIT
	fmc_nwait.SetPullMode(GPIOPin::PULL_UP);

	InitFMCForFPGA();

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
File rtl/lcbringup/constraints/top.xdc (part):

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set_property IOSTANDARD LVCMOS33 [get_ports fmc_noe]
set_property IOSTANDARD LVCMOS33 [get_ports fmc_nwait]
set_property IOSTANDARD LVCMOS33 [get_ports fmc_nwe]
set_property PACKAGE_PIN J19 [get_ports fmc_clk]
set_property PACKAGE_PIN E22 [get_ports fmc_ne1]
set_property PACKAGE_PIN E21 [get_ports fmc_ne3]
set_property PACKAGE_PIN K22 [get_ports fmc_nl_nadv]
set_property PACKAGE_PIN J21 [get_ports fmc_ne2]
set_property PACKAGE_PIN J20 [get_ports fmc_noe]
set_property PACKAGE_PIN G20 [get_ports fmc_nwait]
set_property PACKAGE_PIN H22 [get_ports fmc_nwe]
set_property IOSTANDARD LVCMOS33 [get_ports eth_mdc]

set_property PACKAGE_PIN W22 [get_ports eth_mdc]
set_property IOSTANDARD LVCMOS33 [get_ports mdio]
set_property IOSTANDARD LVCMOS33 [get_ports mdio_tx_en]
set_property PACKAGE_PIN V22 [get_ports mdio_tx_en]
set_property PACKAGE_PIN Y22 [get_ports mdio]

########################################################################################################################
# Clocks
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set_property BITSTREAM.CONFIG.USR_ACCESS TIMESTAMP [current_design]

set_property PACKAGE_PIN F6 [get_ports gtp_refclk_p]
set_property PACKAGE_PIN A8 [get_ports sfp_rx_n]
create_clock -period 6.400 -name gtp_refclk_p -waveform {0.000 3.200} [get_ports gtp_refclk_p]

set_clock_groups -asynchronous -group [get_clocks clkout0] -group [get_clocks clkout0_1]
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
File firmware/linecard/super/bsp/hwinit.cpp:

/***********************************************************************************************************************
*                                                                                                                      *
* LATENTRED                                                                                                            *
*                                                                                                                      *
* Copyright (c) 2023-2025 Andrew D. Zonenberg and contributors                                                         *
* All rights reserved.                                                                                                 *
*                                                                                                                      *
* Redistribution and use in source and binary forms, with or without modification, are permitted provided that the     *
* following conditions are met:                                                                                        *
*                                                                                                                      *
*    * Redistributions of source code must retain the above copyright notice, this list of conditions, and the         *
*      following disclaimer.                                                                                           *
*                                                                                                                      *
*    * Redistributions in binary form must reproduce the above copyright notice, this list of conditions and the       *
*      following disclaimer in the documentation and/or other materials provided with the distribution.                *
*                                                                                                                      *
*    * Neither the name of the author nor the names of any contributors may be used to endorse or promote products     *
*      derived from this software without specific prior written permission.                                           *
*                                                                                                                      *
* THIS SOFTWARE IS PROVIDED BY THE AUTHORS "AS IS" AND ANY EXPRESS OR IMPLIED WARRANTIES, INCLUDING, BUT NOT LIMITED   *
* TO, THE IMPLIED WARRANTIES OF MERCHANTABILITY AND FITNESS FOR A PARTICULAR PURPOSE ARE DISCLAIMED. IN NO EVENT SHALL *
* THE AUTHORS BE HELD LIABLE FOR ANY DIRECT, INDIRECT, INCIDENTAL, SPECIAL, EXEMPLARY, OR CONSEQUENTIAL DAMAGES        *
* (INCLUDING, BUT NOT LIMITED TO, PROCUREMENT OF SUBSTITUTE GOODS OR SERVICES; LOSS OF USE, DATA, OR PROFITS; OR       *
* BUSINESS INTERRUPTION) HOWEVER CAUSED AND ON ANY THEORY OF LIABILITY, WHETHER IN CONTRACT, STRICT LIABILITY, OR TORT *
* (INCLUDING NEGLIGENCE OR OTHERWISE) ARISING IN ANY WAY OUT OF THE USE OF THIS SOFTWARE, EVEN IF ADVISED OF THE       *
* POSSIBILITY OF SUCH DAMAGE.                                                                                          *
*                                                                                                                      *
***********************************************************************************************************************/

/**
	@file
	@author	Andrew D. Zonenberg
	@brief	Boot-time hardware initialization
 */
#include <core/platform.h>
#include <supervisor/supervisor-common.h>
#include "hwinit.h"
#include <peripheral/Power.h>

void InitSPI();
void InitRailSensors();

////////////////////////////////////////////////////////////////////////////////////////////////////////////////////////
// System status indicator LEDs

GPIOPin g_faultLED(&GPIOA, 2, GPIOPin::MODE_OUTPUT, GPIOPin::SLEW_SLOW);
GPIOPin g_sysokLED(&GPIOA, 1, GPIOPin::MODE_OUTPUT, GPIOPin::SLEW_SLOW);
GPIOPin g_pgoodLED(&GPIOA, 0, GPIOPin::MODE_OUTPUT, GPIOPin::SLEW_SLOW);

////////////////////////////////////////////////////////////////////////////////////////////////////////////////////////
// Common global hardware config used by both bootloader and application

//UART console
//USART1 is on APB1 (80 MHz), so we need a divisor of 694.44, round to 694
UART<16, 256> g_uart(&USART1, 694);

//SPI bus to the main MCU
SPI<64, 64> g_spi(&SPI1, true, 2, false);

//I2C1 defaults to running of APB clock (80 MHz)
//Prescale by 4 to get 20 MHz
//Divide by 50 after that to get 400 kHz
I2C g_i2c(&I2C1, 4, 50);

////////////////////////////////////////////////////////////////////////////////////////////////////////////////////////
// Low level init

void BSP_InitUART()
{
	//Initialize the UART for local console: 115.2 Kbps
	//TODO: nice interface for enabling UART interrupts
	GPIOPin uart_tx(&GPIOA, 9, GPIOPin::MODE_PERIPHERAL, GPIOPin::SLEW_SLOW, 7);
	GPIOPin uart_rx(&GPIOA, 10, GPIOPin::MODE_PERIPHERAL, GPIOPin::SLEW_SLOW, 7);

	g_logTimer.Sleep(10);	//wait for UART pins to be high long enough to remove any glitches during powerup

	//Enable the UART interrupt
	NVIC_EnableIRQ(37);
}

////////////////////////////////////////////////////////////////////////////////////////////////////////////////////////
// Common features shared by both application and bootloader

void BSP_Init()
{
	//Bring up the IBC before powering up the rest of the system
	InitGPIOs();
	Super_Init();
	InitSPI();

	App_Init();
}

void InitSPI()
{
	g_log("Initializing management SPI bus\n");

	//Set up GPIOs for management bus
	static GPIOPin mgmt_sck(&GPIOA, 5, GPIOPin::MODE_PERIPHERAL, GPIOPin::SLEW_FAST, 5);
	static GPIOPin mgmt_mosi(&GPIOA, 7, GPIOPin::MODE_PERIPHERAL, GPIOPin::SLEW_FAST, 5);
	static GPIOPin mgmt_cs_n(&GPIOA, 4, GPIOPin::MODE_PERIPHERAL, GPIOPin::SLEW_FAST, 5);
	static GPIOPin mgmt_miso(&GPIOA, 6, GPIOPin::MODE_PERIPHERAL, GPIOPin::SLEW_FAST, 5);

	//Save the CS# pin
	g_spiCS = &mgmt_cs_n;

	//Set up IRQ6 for SPI CS# (PA4) change
	RCCHelper::EnableSyscfg();
	NVIC_EnableIRQ(10);
	EXTI::SetExtInterruptMux(4, EXTI::PORT_A);
	EXTI::EnableChannel(4);
	EXTI::EnableFallingEdgeTrigger(4);

	//Set up IRQ35 as SPI1 interrupt
	NVIC_EnableIRQ(35);
	g_spi.EnableRxInterrupt();
}

////////////////////////////////////////////////////////////////////////////////////////////////////////////////////////
// GPIOs for all of the rail enables

void InitGPIOs()
{
	g_log("Initializing GPIOs\n");

	//turn off all LEDs
	g_faultLED = 0;
	g_sysokLED = 0;

	//Set up GPIOs for I2C bus
	static GPIOPin i2c_scl(&GPIOB, 6, GPIOPin::MODE_PERIPHERAL, GPIOPin::SLEW_SLOW, 4, true);
	static GPIOPin i2c_sda(&GPIOB, 7, GPIOPin::MODE_PERIPHERAL, GPIOPin::SLEW_SLOW, 4, true);
}
